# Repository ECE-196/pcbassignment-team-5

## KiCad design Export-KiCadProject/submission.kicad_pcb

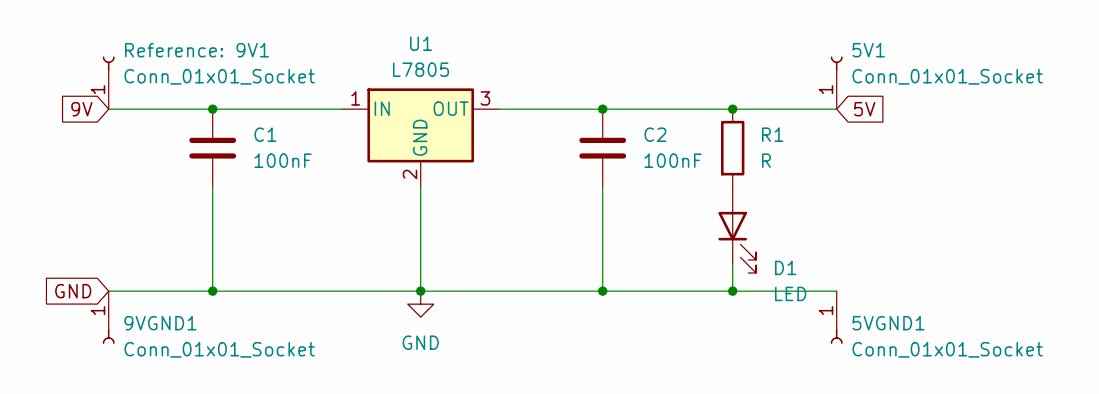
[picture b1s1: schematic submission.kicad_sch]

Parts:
5V1, 5VGND1, 9V1, 9VGND1: Conn_01x01_Socket; PinSocket_1x01_P2.00mm_Horizontal
C1, C2: 100nF; CP_Radial_D8.0mm_P3.50mm
D1: LED; LED_0805_2012Metric
R1: R; R_0805_2012Metric
U1: L7805; TO-220-3_Horizontal_TabUp

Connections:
5V: 5V1.1, C2.1, R1.1, U1.3 (OUT)
9V: 9V1.1, C1.1, U1.1 (IN)
GND: 5VGND1.1, 9VGND1.1, C1.2, C2.2, D1.1 (K), U1.2 (GND)
unnamed: D1.2 (A), R1.2

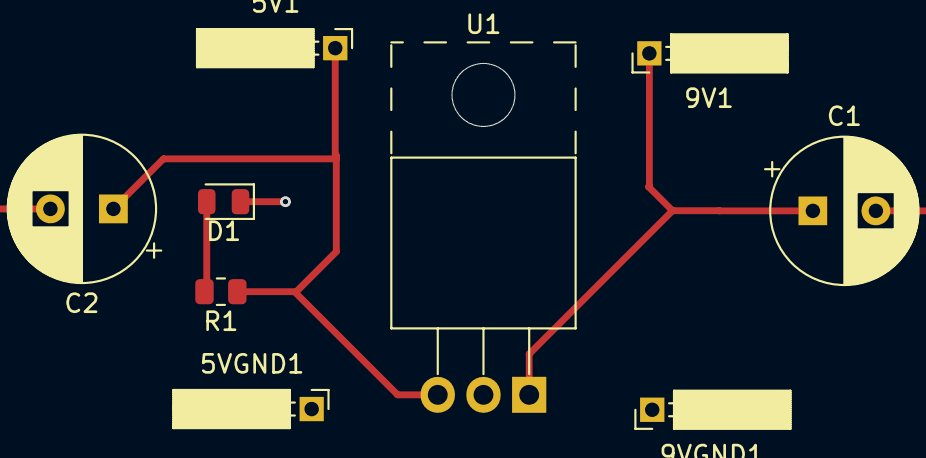
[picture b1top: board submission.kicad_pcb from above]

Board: 2 copper layers, 9 parts (0 on the bottom side), 4 nets.

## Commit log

2024-04-28 add deadline
2024-04-29 uploading submission
